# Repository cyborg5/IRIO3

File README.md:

# IRIO3
## Infrared send and receive board

This open source circuit board provides input and output capabilities for use with IRLib2 library for Arduino.

Download IRLib at [https://github.com/cyborg5/IRLib2](https://github.com/cyborg5/IRLib2).

See a complete tutorial for this board at [https://learn.adafruit.com/building-an-infrared-transmitter-and-receiver-board/](https://learn.adafruit.com/building-an-infrared-transmitter-and-receiver-board/) coming soon.

Included in this repository
 - IRIO3.brd Eagle CAD board file
 - IRIO3.sch Eagle CAD schematic
 - IRIO3_2019-08-19.zip Gerber files created from Eagle CAD
 - IRIO3.f3z Fusion 360 model

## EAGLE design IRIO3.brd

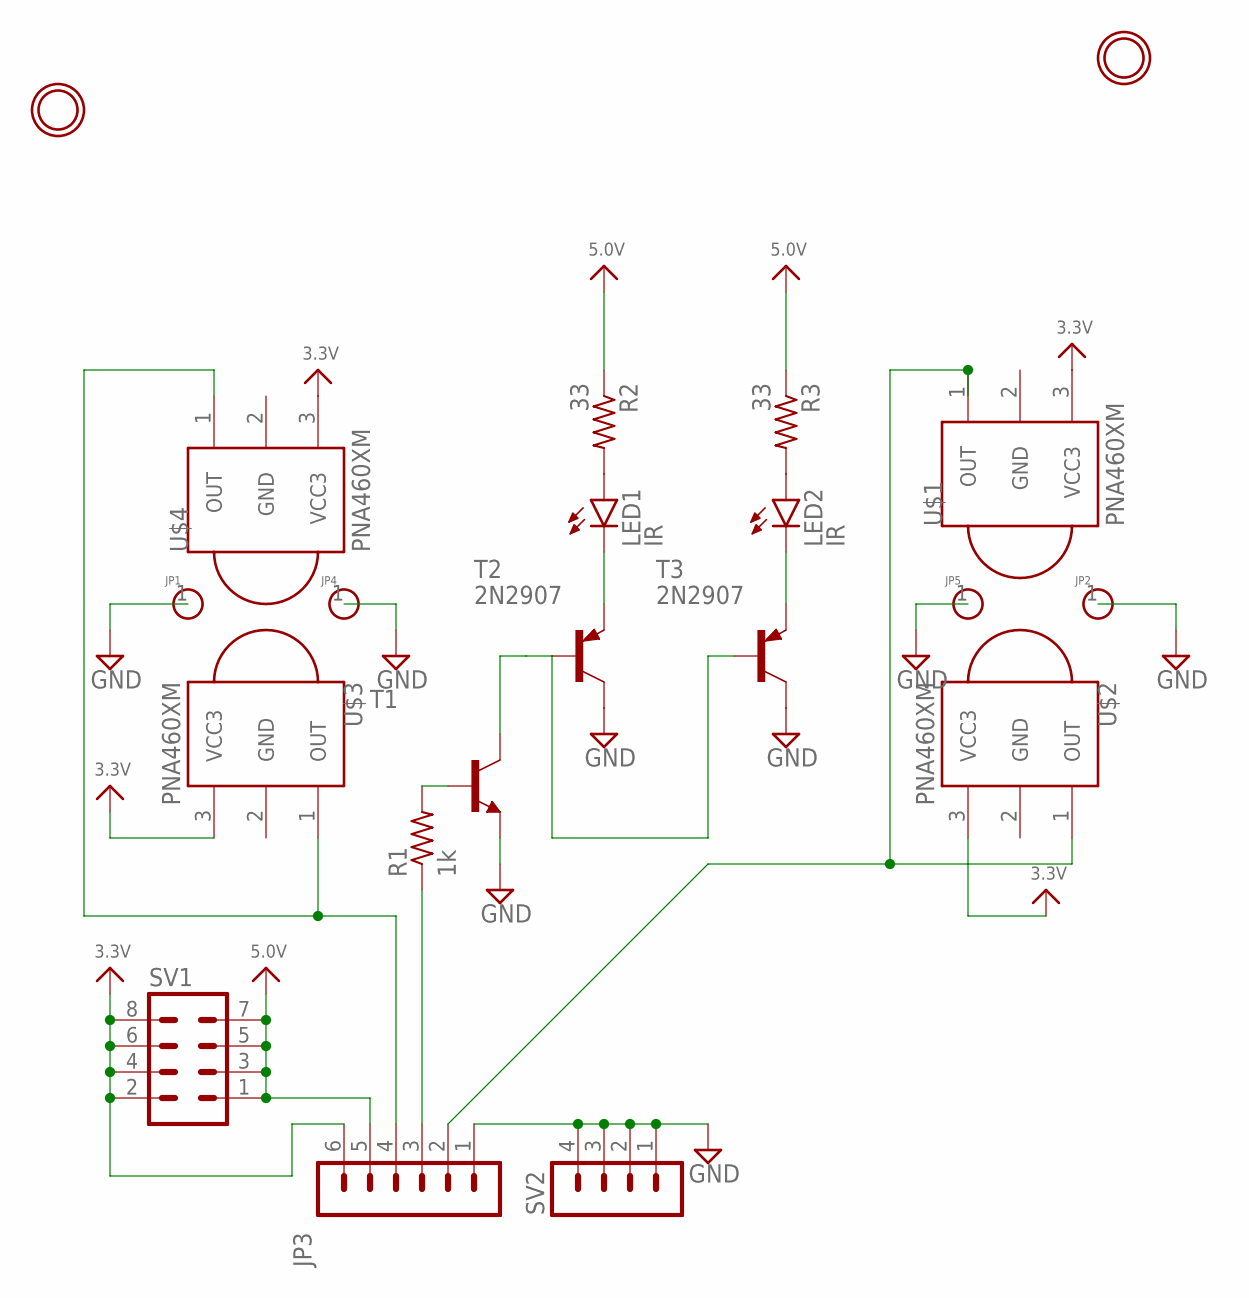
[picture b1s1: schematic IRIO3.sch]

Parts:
JP1, JP2, JP4, JP5: HOLE-DEV; HOLE-PAH
JP3: MA06-1
LED1, LED2: IR; LED3MM
R1: 1k; 0207/10
R2, R3: 33; 0204V
SV1: MA04-2
SV2: MA04-1
T1: -NPN-TO92-EBC; TO92-EBC
T2, T3: 2N2907; TO92-CBE
U$1, U$2, U$3, U$4: PNA460XM
U$7, U$8: MOUNTINGHOLE2.0; MOUNTINGHOLE_2.0_PLATED

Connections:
GND: JP1.1, JP2.1, JP3.1, JP4.1, JP5.1, SV2.1, SV2.2, SV2.3, SV2.4, T1.E, T2.C, T3.C, U$1.2 (GND), U$2.2 (GND), U$3.2 (GND), U$4.2 (GND)
unnamed: JP3.3, R1.1
unnamed: JP3.4, U$3.1 (OUT), U$4.1 (OUT)
unnamed: R1.2, T1.B
unnamed: LED2.K (C), T3.E
unnamed: JP3.2, U$1.1 (OUT), U$2.1 (OUT)
unnamed: LED1.K (C), T2.E
unnamed: T1.C, T2.B, T3.B
unnamed: LED2.A, R3.2
unnamed: LED1.A, R2.2
VCC3: JP3.6, SV1.2, SV1.4, SV1.6, SV1.8, U$1.3 (VCC3), U$2.3 (VCC3), U$3.3 (VCC3), U$4.3 (VCC3)
VCC5: JP3.5, R2.1, R3.1, SV1.1, SV1.3, SV1.5, SV1.7

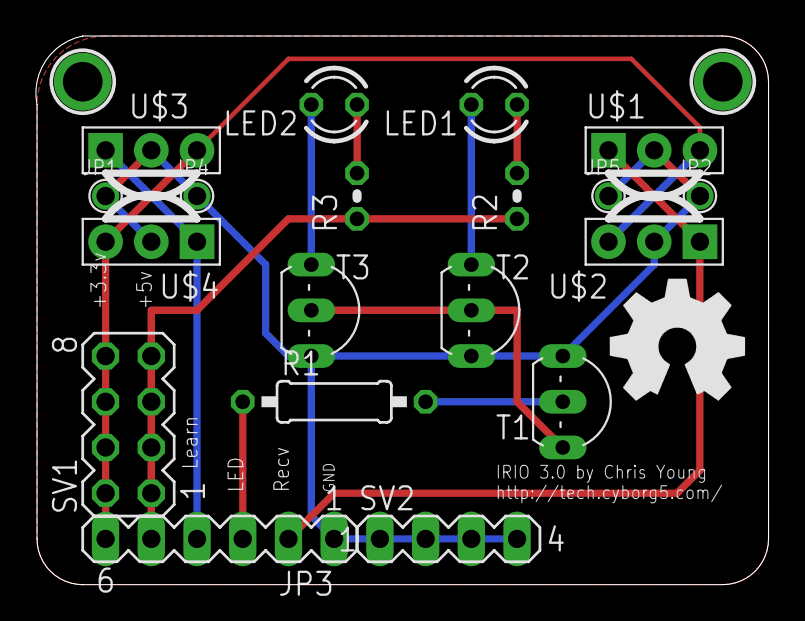
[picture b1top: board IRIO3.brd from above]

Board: 2 copper layers, 40.7 x 30.5 mm, 21 parts (0 on the bottom side), 12 nets.

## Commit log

2019-08-19 Initial release
    Initial release
2019-08-20 Added fusion 360 file

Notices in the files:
parts and their libraries:
microbuilder: This work is placed in the public domain, and may be freely used for commercial and non-commercial work with the following conditions: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
